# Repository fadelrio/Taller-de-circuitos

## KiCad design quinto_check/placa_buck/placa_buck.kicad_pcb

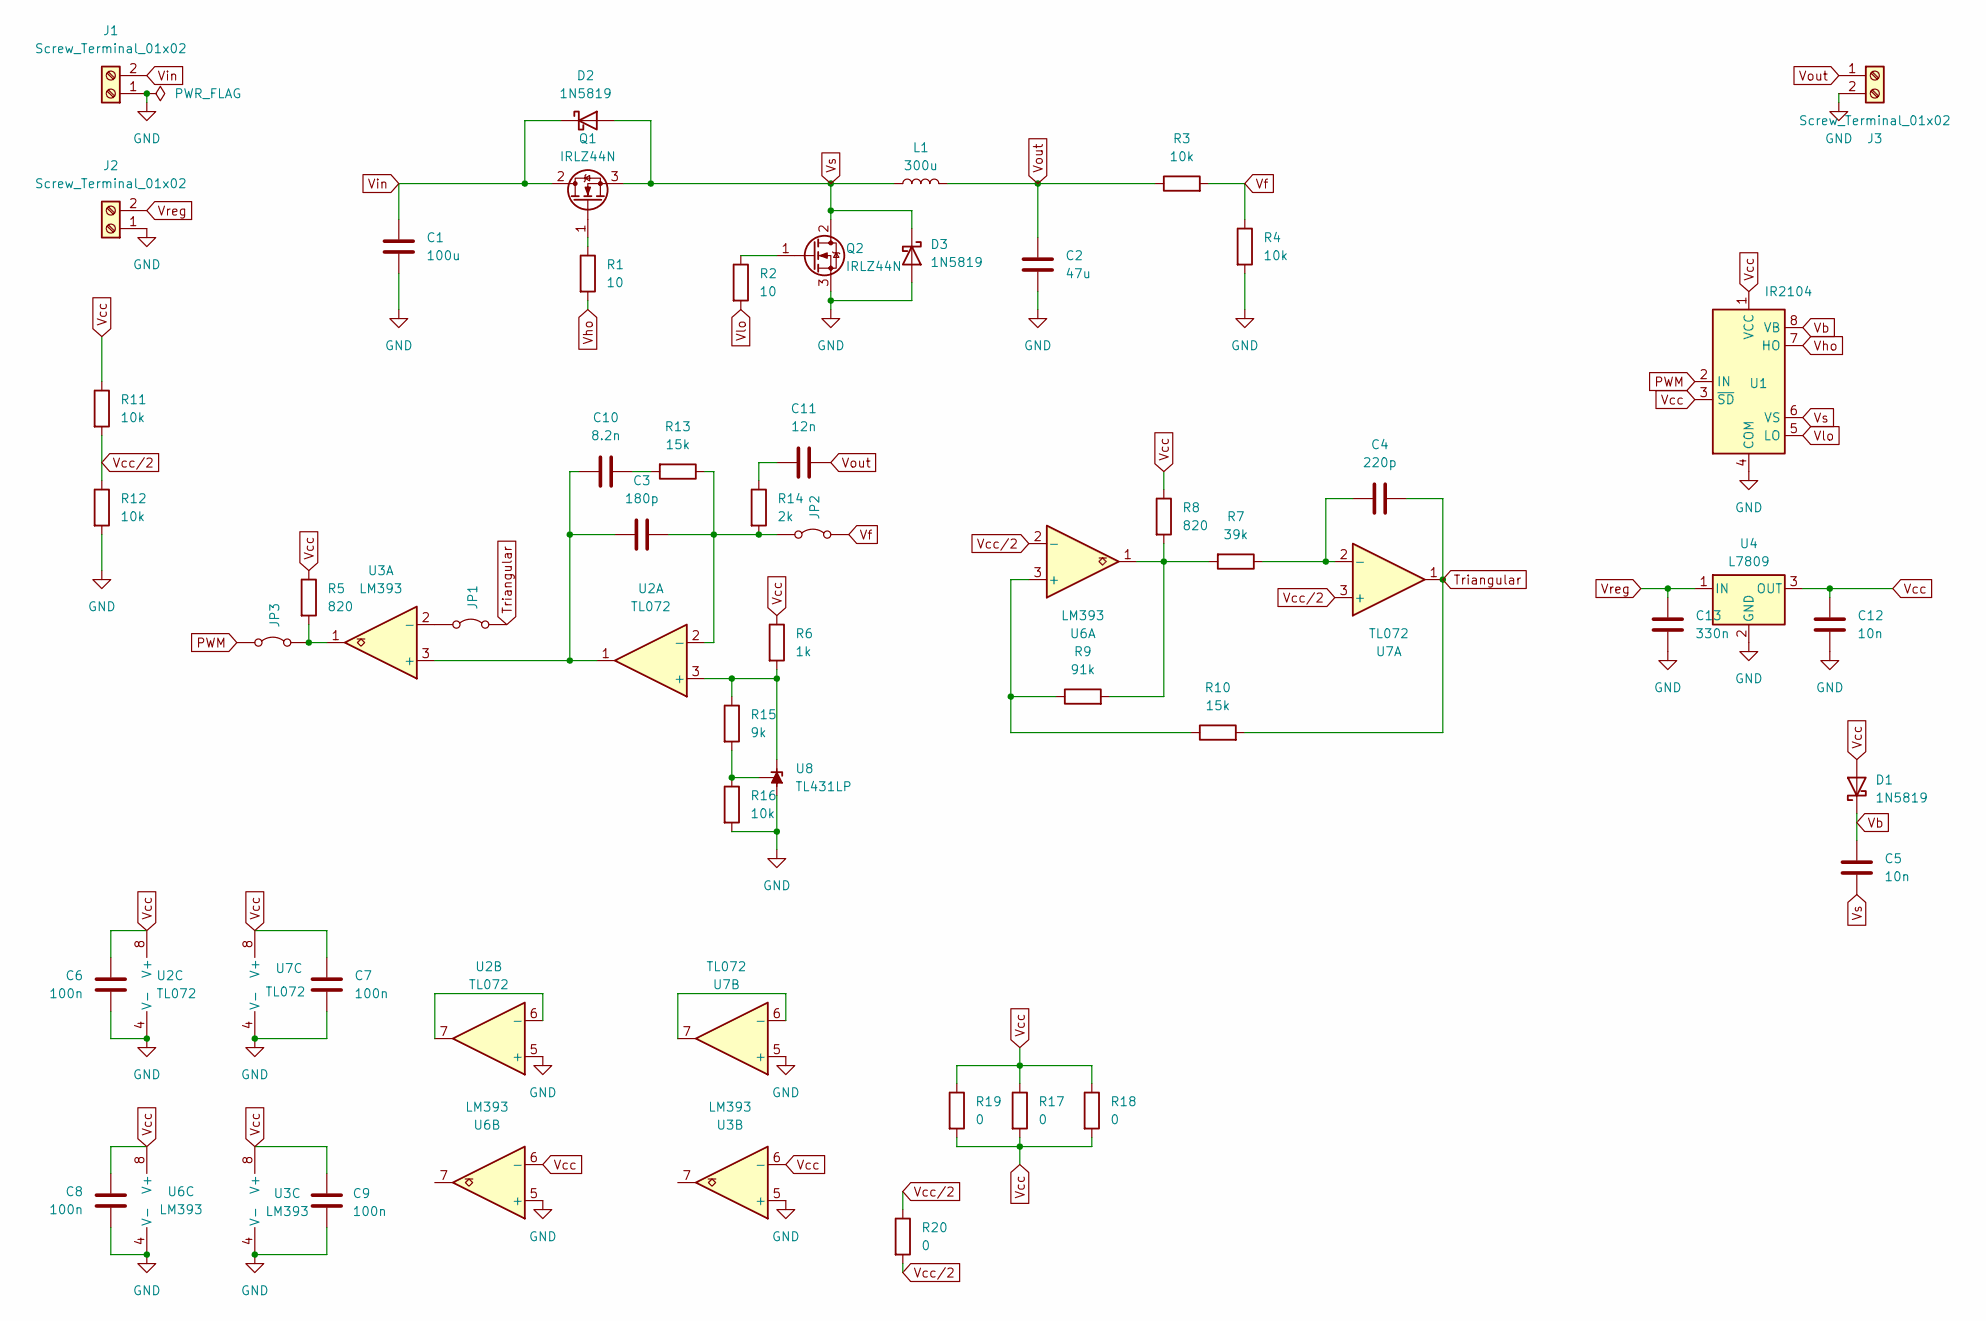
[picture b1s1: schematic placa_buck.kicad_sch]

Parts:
C1: 100u; CP_Radial_D4.0mm_P2.00mm
C2: 47u; CP_Radial_D4.0mm_P2.00mm
C3: 180p; C_Disc_D4.3mm_W1.9mm_P5.00mm
C4: 220p; C_Disc_D4.3mm_W1.9mm_P5.00mm
C5, C12: 10n; C_Disc_D4.3mm_W1.9mm_P5.00mm
C6, C7, C8, C9: 100n; C_Disc_D4.3mm_W1.9mm_P5.00mm
C10: 8.2n; C_Disc_D4.3mm_W1.9mm_P5.00mm
C11: 12n; C_Disc_D4.3mm_W1.9mm_P5.00mm
C13: 330n; C_Disc_D4.3mm_W1.9mm_P5.00mm
D1, D2, D3: 1N5819; D_DO-41_SOD81_P10.16mm_Horizontal
J1, J2, J3: Screw_Terminal_01x02; Samtec_HPM-02-01-x-S_Straight_1x02_Pitch5.08mm
JP1, JP2, JP3: Jumper_2_Bridged; TestPoint_2Pads_Pitch2.54mm_Drill0.8mm
L1: 300u; Transformer_Breve_TEZ-35x42
Q1, Q2: IRLZ44N; TO-220-3_Vertical
R1, R2: 10; R_Axial_DIN0207_L6.3mm_D2.5mm_P10.16mm_Horizontal
R3, R4, R11, R12, R16: 10k; R_Axial_DIN0207_L6.3mm_D2.5mm_P10.16mm_Horizontal
R5, R8: 820; R_Axial_DIN0207_L6.3mm_D2.5mm_P10.16mm_Horizontal
R6: 1k; R_Axial_DIN0207_L6.3mm_D2.5mm_P10.16mm_Horizontal
R7: 39k; R_Axial_DIN0207_L6.3mm_D2.5mm_P10.16mm_Horizontal
R9: 91k; R_Axial_DIN0207_L6.3mm_D2.5mm_P10.16mm_Horizontal
R10, R13: 15k; R_Axial_DIN0207_L6.3mm_D2.5mm_P10.16mm_Horizontal
R14: 2k; R_Axial_DIN0207_L6.3mm_D2.5mm_P10.16mm_Horizontal
R15: 9k; R_Axial_DIN0207_L6.3mm_D2.5mm_P10.16mm_Horizontal
R17, R18, R19, R20: 0; R_Axial_DIN0207_L6.3mm_D2.5mm_P10.16mm_Horizontal
U1: IR2104; DIP-8_W7.62mm_LongPads
U2, U7: TL072; DIP-8_W7.62mm_LongPads
U3, U6: LM393; DIP-8_W7.62mm_LongPads
U4: L7809; TO-220-3_Vertical
U8: TL431LP; TO-92L_Inline_Wide

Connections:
GND: C1.2, C2.2, C6.2, C7.2, C8.2, C9.2, C12.2, C13.2, D3.2 (A), J1.1, J2.1, J3.2, Q2.3 (S), R4.2, R12.2, R16.2, U1.4 (COM), U2.4 (V-), U2.5 (+), U3.4 (V-), U3.5 (+), U4.2 (GND), U6.4 (V-), U6.5 (+), U7.4 (V-), U7.5 (+), U8.2 (A)
unnamed: C10.1, R13.2
unnamed: C11.2, R14.1
unnamed: JP1.1 (A), U3.2 (-)
unnamed: C3.2, JP2.1 (A), R13.1, R14.2, U2.2 (-)
unnamed: JP3.2 (B), R5.2, U3.1
unnamed: Q1.1 (G), R1.1
unnamed: Q2.1 (G), R2.1
unnamed: R7.2, R8.2, R9.2, U6.1
unnamed: R6.2, R15.1, U2.3 (+), U8.3 (K)
unnamed: U2.6 (-), U2.7
unnamed: C3.1, C10.2, U2.1, U3.3 (+)
unnamed: R9.1, R10.1, U6.3 (+)
unnamed: C4.1, R7.1, U7.2 (-)
unnamed: U7.6 (-), U7.7
unnamed: R15.2, R16.1, U8.1 (REF)
PWM: JP3.1 (A), U1.2 (IN)
Triangular: C4.2, JP1.2 (B), R10.2, U7.1
Vb: C5.1, D1.1 (K), U1.8 (VB)
Vcc: C6.1, C7.1, C8.1, C9.1, C12.1, D1.2 (A), R5.1, R6.1, R8.1, R11.1, R17.1, R17.2, R18.1, R18.2, R19.1, R19.2, U1.1 (VCC), U1.3 (~SD), U2.8 (V+), U3.6 (-), U3.8 (V+), U4.3 (OUT), U6.6 (-), U6.8 (V+), U7.8 (V+)
Vcc/2: R11.2, R12.1, R20.1, R20.2, U6.2 (-), U7.3 (+)
Vf: JP2.2 (B), R3.2, R4.1
Vho: R1.2, U1.7 (HO)
Vin: C1.1, D2.1 (K), J1.2, Q1.2 (D)
Vlo: R2.2, U1.5 (LO)
Vout: C2.1, C11.1, J3.1, L1.2, R3.1
Vreg: C13.1, J2.2, U4.1 (IN)
Vs: C5.2, D2.2 (A), D3.1 (K), L1.1, Q1.3 (S), Q2.2 (D), U1.6 (VS)

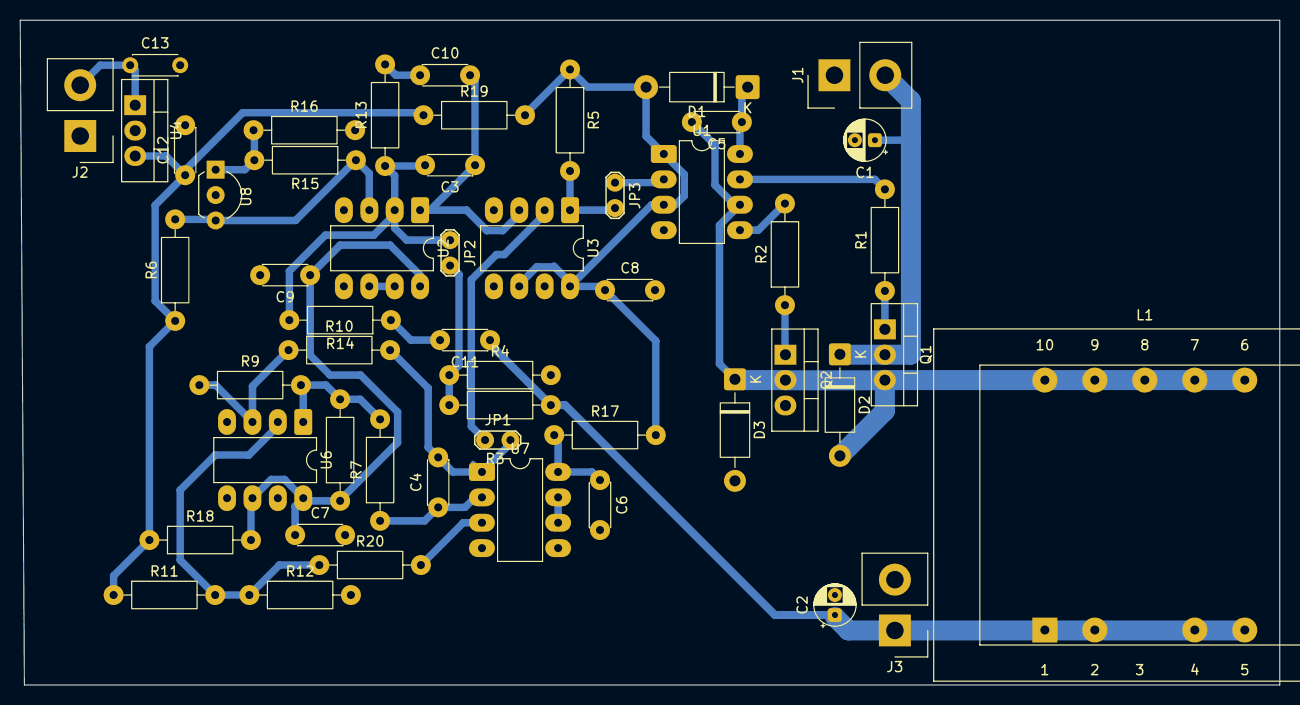
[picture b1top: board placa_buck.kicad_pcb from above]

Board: 2 copper layers, 126.0 x 66.5 mm, 52 parts (0 on the bottom side), 28 nets.

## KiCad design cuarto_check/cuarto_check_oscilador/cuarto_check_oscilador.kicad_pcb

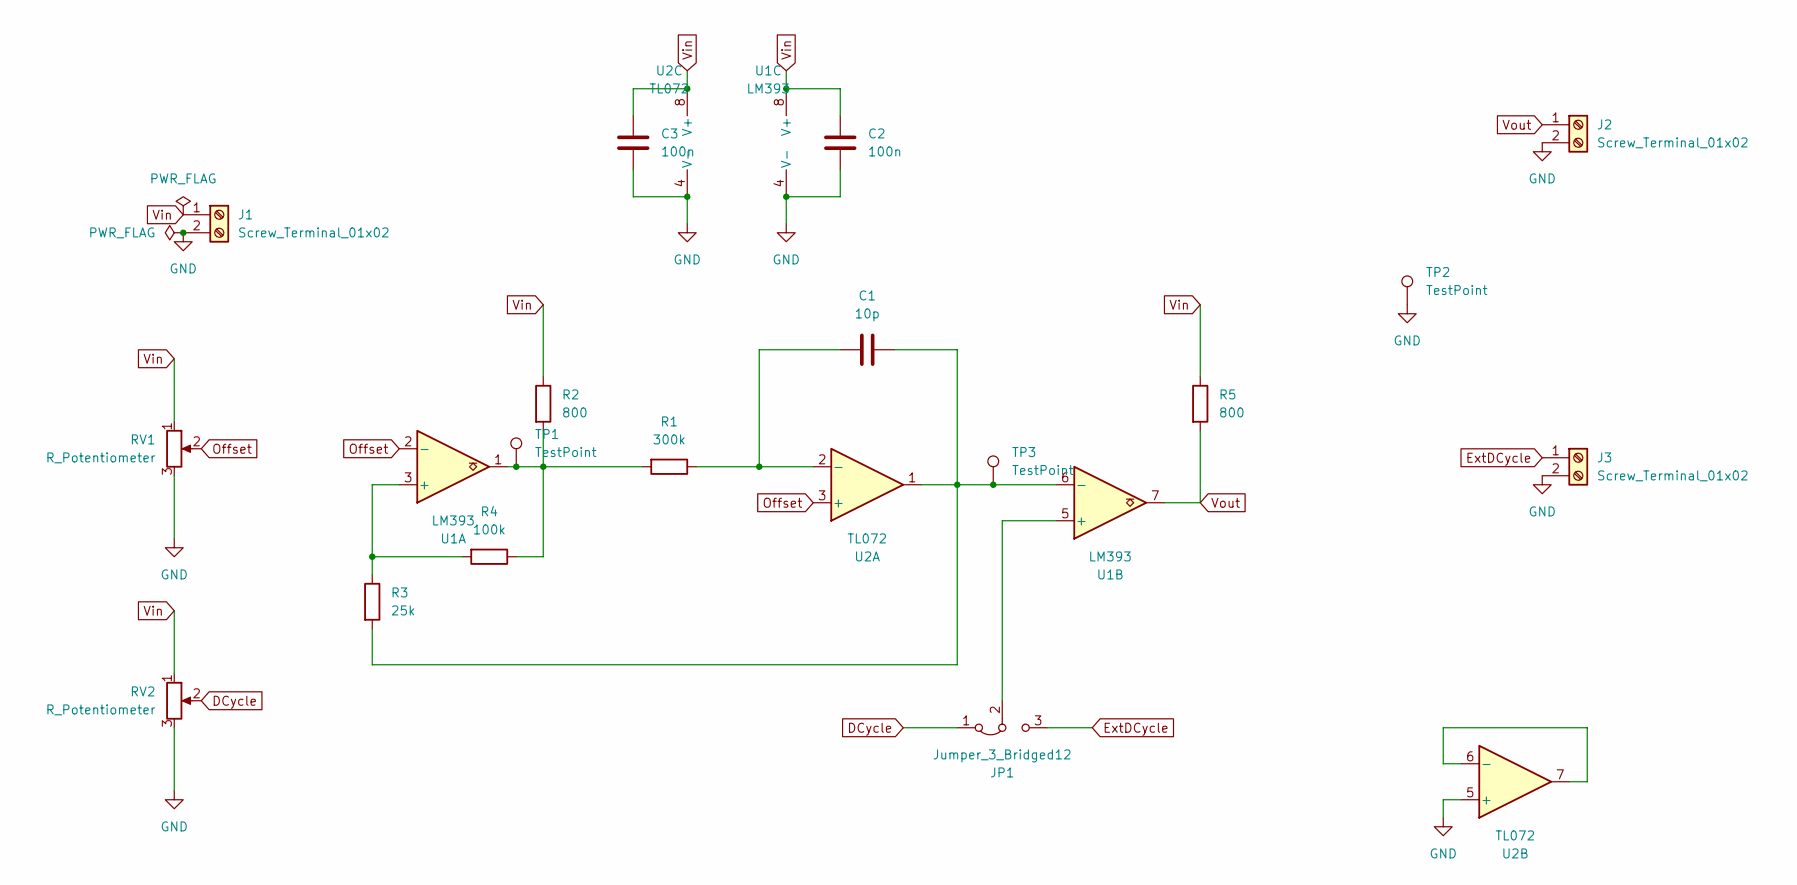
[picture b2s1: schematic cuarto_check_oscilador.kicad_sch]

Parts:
C1: 10p; C_Disc_D4.3mm_W1.9mm_P5.00mm
C2, C3: 100n; C_Disc_D4.3mm_W1.9mm_P5.00mm
J1, J2, J3: Screw_Terminal_01x02; Samtec_HPM-02-01-x-S_Straight_1x02_Pitch5.08mm
JP1: Jumper_3_Bridged12; PinHeader_1x03_P2.54mm_Vertical
R1: 300k; R_Axial_DIN0207_L6.3mm_D2.5mm_P10.16mm_Horizontal
R2, R5: 800; R_Axial_DIN0207_L6.3mm_D2.5mm_P10.16mm_Horizontal
R3: 25k; R_Axial_DIN0207_L6.3mm_D2.5mm_P10.16mm_Horizontal
R4: 100k; R_Axial_DIN0207_L6.3mm_D2.5mm_P10.16mm_Horizontal
RV1, RV2: R_Potentiometer; Potentiometer_Bourns_3266Y_Vertical
TP1, TP2, TP3: TestPoint; TestPoint_Loop_D2.54mm_Drill1.5mm_Beaded
U1: LM393; DIP-8_W7.62mm_LongPads
U2: TL072; DIP-8_W7.62mm_LongPads

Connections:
DCycle: JP1.1 (A), RV2.2
ExtDCycle: J3.1, JP1.3 (B)
GND: C2.1, C3.1, J1.2, J2.2, J3.2, RV1.3, RV2.3, TP2.1, U1.4 (V-), U2.4 (V-), U2.5 (+)
unnamed: JP1.2 (C), U1.5 (+)
unnamed: R1.2, R2.2, R4.1, TP1.1, U1.1
unnamed: R3.1, R4.2, U1.3 (+)
unnamed: C1.1, R3.2, TP3.1, U1.6 (-), U2.1
unnamed: C1.2, R1.1, U2.2 (-)
unnamed: U2.6 (-), U2.7
Offset: RV1.2, U1.2 (-), U2.3 (+)
Vin: C2.2, C3.2, J1.1, R2.1, R5.1, RV1.1, RV2.1, U1.8 (V+), U2.8 (V+)
Vout: J2.1, R5.2, U1.7

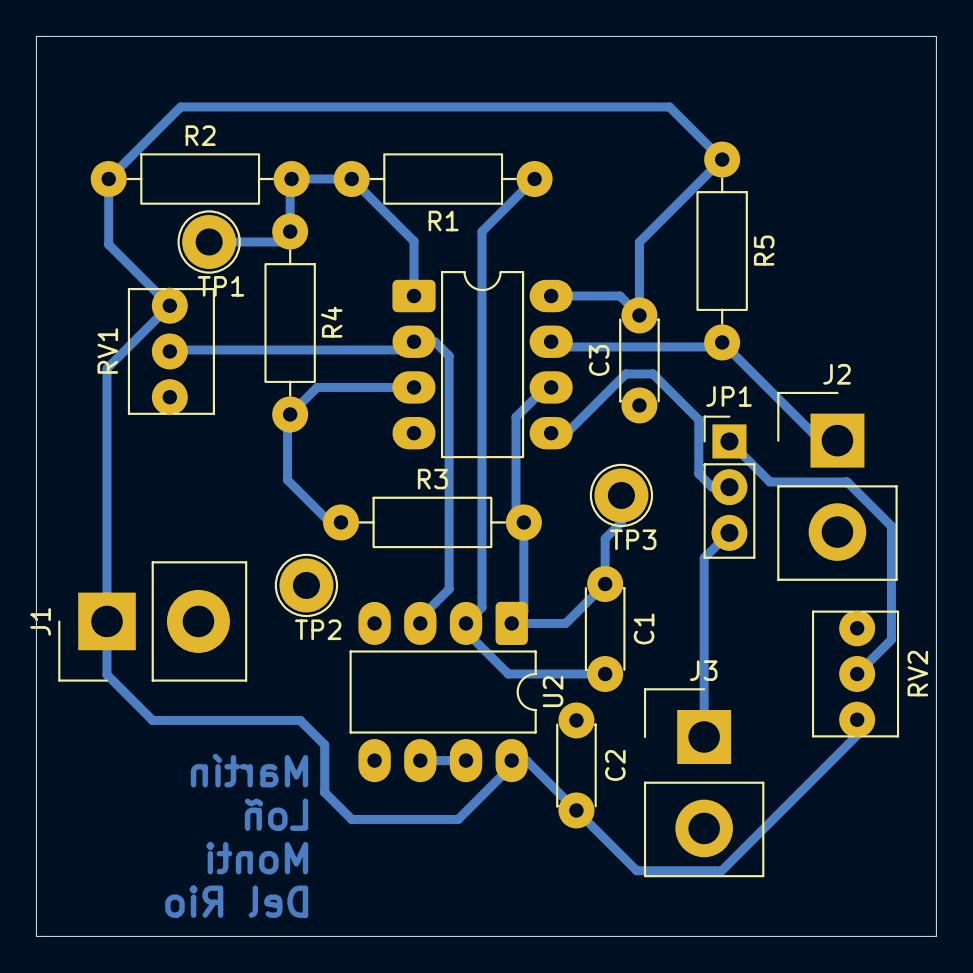
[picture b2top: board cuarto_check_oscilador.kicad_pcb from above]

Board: 2 copper layers, 50.0 x 50.0 mm, 19 parts (0 on the bottom side), 12 nets.

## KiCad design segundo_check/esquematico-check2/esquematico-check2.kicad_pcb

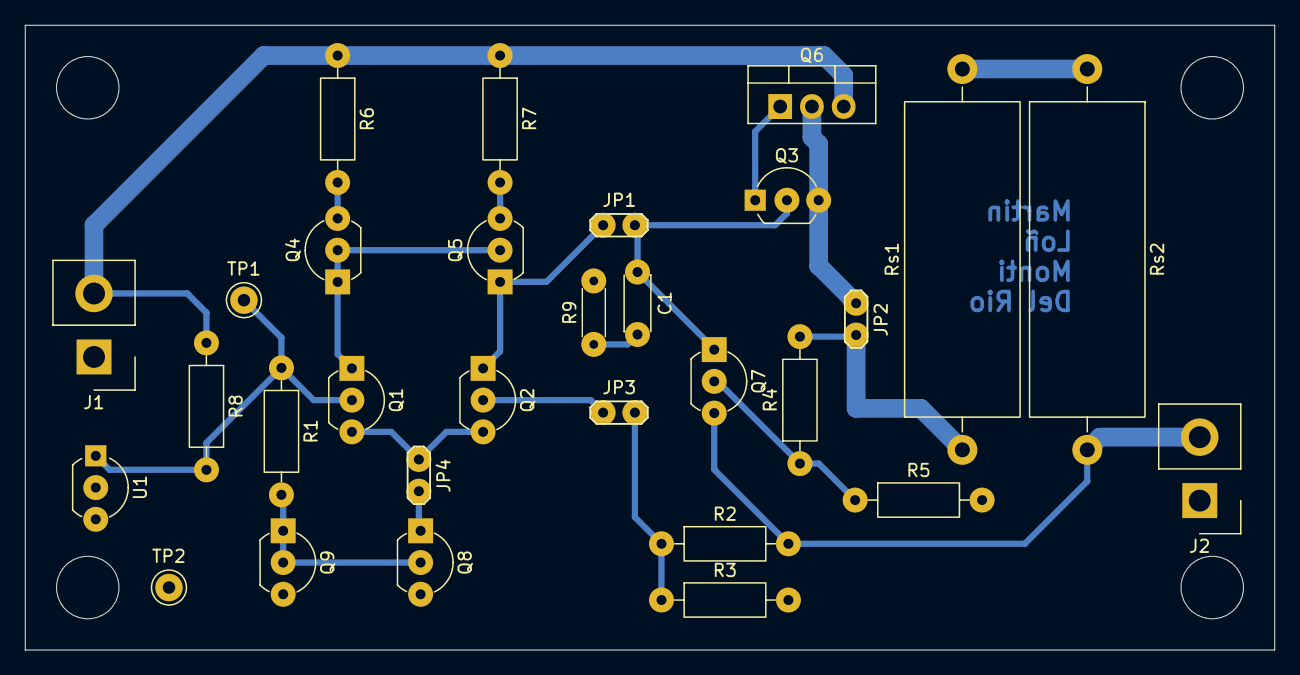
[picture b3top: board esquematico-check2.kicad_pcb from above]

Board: 2 copper layers, 100.0 x 50.0 mm, 30 parts (0 on the bottom side), 20 nets.

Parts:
C1: C; C_Disc_D4.3mm_W1.9mm_P5.00mm
J1, J2: Conn_01x02; Samtec_HPM-02-01-x-S_Straight_1x02_Pitch5.08mm
JP1, JP2, JP3, JP4: Jumper_2_Bridged; TestPoint_2Pads_Pitch2.54mm_Drill0.8mm
Q1, Q2, Q3, Q7, Q8, Q9: BC547; TO-92_Inline_Wide
Q4, Q5: BC557; TO-92_Inline_Wide
Q6: MJE2955T; TO-220-3_Vertical
R1: 1.8k; R_Axial_DIN0207_L6.3mm_D2.5mm_P10.16mm_Horizontal
R2, R3: 2K; R_Axial_DIN0207_L6.3mm_D2.5mm_P10.16mm_Horizontal
R4, R8: 1k; R_Axial_DIN0207_L6.3mm_D2.5mm_P10.16mm_Horizontal
R5: 1880; R_Axial_DIN0207_L6.3mm_D2.5mm_P10.16mm_Horizontal
R6, R7: 100; R_Axial_DIN0207_L6.3mm_D2.5mm_P10.16mm_Horizontal
R9: R; R_Axial_DIN0204_L3.6mm_D1.6mm_P5.08mm_Horizontal
Rs1, Rs2: 1.2; R_Axial_Power_L25.0mm_W9.0mm_P30.48mm
TP1, TP2: TestPoint_Probe; TestPoint_Keystone_5000-5004_Miniature
U1: TL431D; TO-92_Inline_Wide

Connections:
GND: J1.1, J2.1, Q8.3 (E), Q9.3 (E), R3.2, R5.2, R9.2, TP2.1, U1.2 (A), U1.3 (A)
unnamed: C1.2, R9.1
unnamed: J1.2, Q6.3 (E), R6.1, R7.1, R8.1
unnamed: J2.2, Q7.3 (E), R2.2, Rs2.2
unnamed: JP1.1 (A), Q2.1 (C), Q5.1 (C)
unnamed: C1.1, JP1.2 (B), Q3.2 (B), Q7.1 (C)
unnamed: JP2.1 (A), Q3.3 (E), Q6.2 (C)
unnamed: JP2.2 (B), R4.2, Rs1.1
unnamed: JP3.1 (A), Q2.2 (B)
unnamed: JP3.2 (B), R2.1, R3.1
unnamed: JP4.1 (A), Q1.3 (E), Q2.3 (E)
unnamed: JP4.2 (B), Q8.1 (C)
unnamed: Q1.2 (B), R1.1, R8.2, TP1.1, U1.1 (K)
unnamed: Q1.1 (C), Q4.1 (C), Q4.2 (B), Q5.2 (B)
unnamed: Q3.1 (C), Q6.1 (B)
unnamed: Q4.3 (E), R6.2
unnamed: Q5.3 (E), R7.2
unnamed: Q7.2 (B), R4.1, R5.1
unnamed: Q8.2 (B), Q9.1 (C), Q9.2 (B), R1.2
unnamed: Rs1.2, Rs2.1

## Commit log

2025-09-06 primer commit
2025-09-08 Algunos graficos de eficiencia
2025-09-09 Soy martu e hice el esquematico de kicad y soy re capa
2025-09-09 esquematico pcb, le falta la resistencia de la ref nomas
2025-09-11 esquematico chk1 terminado
2025-09-11 muchas cosas, graficos, scripts y modificaciones en ltspice
2025-09-11 ahora si el esquematico chk1
2025-09-13 Primer checkpoint
2025-09-19 Inicio segundo checkpoint
2025-09-19 inicio PCB
2025-09-20 Avances PCB
2025-10-01 Placa reglin terminada?
2025-10-01 Post Segundo check
2025-10-06 Detalles previos a impresión de la placa
2025-10-10 Avances carga electronica
2025-10-14 Primeras mediciones y graficos tercer check
2025-10-15 Continuacion check 3
2025-10-17 Cerrando check 3
2025-10-18 Entrega tercer check
2025-10-26 Inicio cuarto check
2025-10-30 Inicio PCB oscilador CP4
2025-10-31 Fin? diseño placa oscilador
2025-11-01 matenme porfa
2025-11-01 A mi también matenme porfa
2025-11-10 Entrega check 4 (faltan cosas)
2025-11-14 Inicio quinto check
2025-12-01 Ya ni se todo lo q hicimos
2025-12-06 Entrega de quinto check
2025-12-10 Espero que sea el ultimo commit
